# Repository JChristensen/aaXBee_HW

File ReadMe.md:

# Double-A XBee Sensor Node #
http://github.com/JChristensen/aaXBee_HW  
ReadMe file  
Jack Christensen Mar 2015  

## Introduction ##
A low-power, [Arduino](http://www.arduino.cc/)-compatible [XBee](http://www.digi.com/products/wireless-wired-embedded-solutions/zigbee-rf-modules/zigbee-mesh-module/xbee-zb-module) sensor node that runs on two AA cells. It should run for over a year on a pair of AA alkaline cells (this could be reduced if sensors that require relatively large amounts of power or on-time are used). For an example sketch, see the [aaXBee sketch](https://github.com/JChristensen/GroveStreams/tree/master/examples/aaXBee) in my [GroveStreams library](https://github.com/JChristensen/GroveStreams). The AA XBee Node will send data to an Arduino running the [gsGateway sketch](https://github.com/JChristensen/GroveStreams/tree/master/examples/gsGateway), which forwards it to the [GroveStreams](https://grovestreams.com/) web site. (Also see my blog post, [A GroveStreams Wireless Sensor Network](http://adventuresinarduinoland.blogspot.com/2015/05/a-grovestreams-wireless-sensor-network.html).)

The AA XBee Node includes an accurate real-time clock ([DS3231](http://www.maximintegrated.com/en/products/digital/real-time-clocks/DS3231.html), ±2ppm from 0°C to +40°C) for precise timing of data transmissions and an accurate on-board I2C temperature sensor ([MCP9808](http://www.microchip.com/MCP9808), ±0.25°C typical). A prototyping area is provided for connecting additional sensors. Twelve microcontroller GPIO pins are available to interface with sensors, including the I2C and SPI buses and analog inputs. A pushbutton switch and an LED are available for application use.

## Features ##
The Double-A XBee Sensor Node is a flexible design with three major configuration options based on the voltage and power required by application-specific sensors. One or two boost regulators are used to supply 3.3V to the XBee and either 3.3V or 5V to the MCU and sensors.These configurations are summarized on page 2 of the [aaXBee_BOM.pdf](http://github.com/JChristensen/aaXBee_HW/raw/master/aaXBee_BOM.pdf) file.

Various components are also optional depending on requirements. See page 3 of the [aaXBee_BOM.pdf](http://github.com/JChristensen/aaXBee_HW/raw/master/aaXBee_BOM.pdf) file for comments on optional components.

To conserve power, the AA XBee Node disables the boost regulator(s) and sleeps using the battery voltage directly (sleep current is < 5µA). With the regulator(s) disabled, the MCU's clock speed is reduced to avoid overclocking. Because of this, the board should be programmed with an in-circuit serial programmer (ICSP, e.g. AVRISP mkII, USBtinyISP, USBasp, etc.) as opposed to a bootloader. As part of this approach, specific fuse settings are required, so a custom entry in the Arduino boards.txt file is also recommended as follows:
```
##############################################################
aaDL.name=Double-A Datalogger/Double-A XBee Node
aaDL.upload.protocol=arduino
aaDL.upload.maximum_size=32768
aaDL.bootloader.low_fuses=0x7f
aaDL.bootloader.high_fuses=0xde
aaDL.bootloader.extended_fuses=0x06
aaDL.build.mcu=atmega328p
aaDL.build.f_cpu=8000000L
aaDL.build.core=arduino
aaDL.build.variant=standard
##############################################################
```

## CC BY-SA ##
"Double-A XBee Sensor Node" by Jack Christensen is licensed under [CC BY-SA 4.0](http://creativecommons.org/licenses/by-sa/4.0/).

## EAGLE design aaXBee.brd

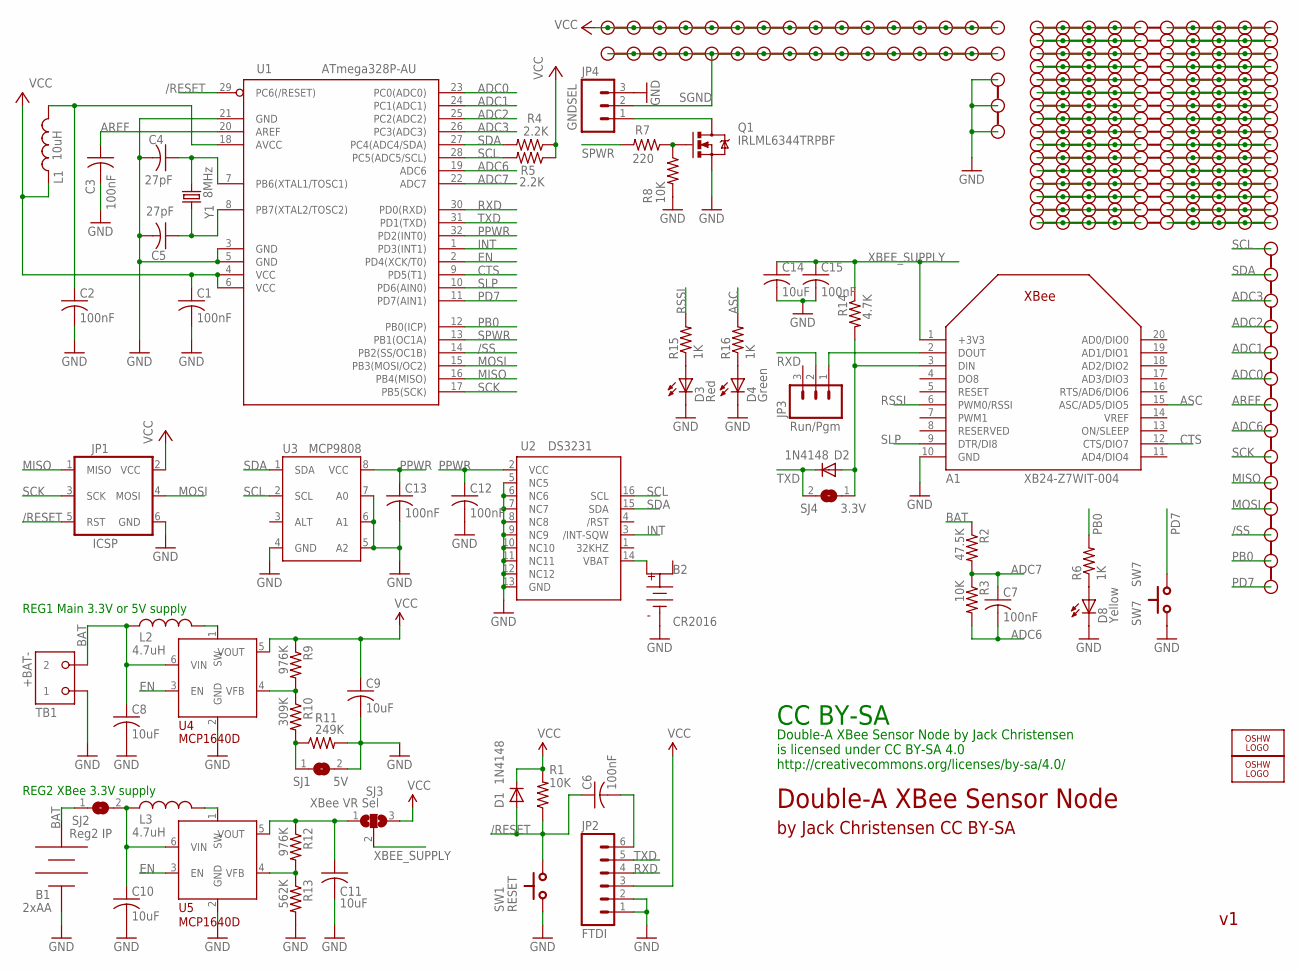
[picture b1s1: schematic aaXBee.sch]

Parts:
A1: XB24-Z7WIT-004; XBEE_OVAL_PADS
B1: 2xAA; KEYSTONE-2462-NO-HOLES
B2: CR2016; BAT-HLD-002-SMT
C1, C2, C3, C6, C7, C12, C13, C15: 100nF; M0805
C4, C5: 27pF; M0805
C8, C9, C10, C11, C14: 10uF; M0805
D1, D2: 1N4148; SOD-323F-A
D3: Red; D0805A
D4: Green; D0805
D8: Yellow; D0805A
JP1: ICSP; 2X3_LOCK
JP2: FTDI; 1X06_LOCK
JP3: Run/Pgm; 1X03_LOCK
JP4: GNDSEL; 1X03_LOCK
L1: 10uH; M0805
L2, L3: 4.7uH; NRS4018
LOGO1, LOGO2: OSHW_LOGO_8MILX0150-NT; OSHW_8X150_NOTEXT
PR1, PR2, PR3, PR4, PR5, PR6, PR7, PR8, PR9, PR10, PR11, PR12, PR14, PR15, PR16, PR17: PROTO-10
PR13: GND; PROTO-3
PR18: Proto ground; PROTO-16
PR19: Proto Vcc; PROTO-16
PR20: Signals; PROTO-14-NR
Q1: IRLML6344TRPBF; SOT23
R1, R3, R8: 10K; M0805
R2: 47.5K; M0805
R4, R5: 2.2K; M0805
R6, R15, R16: 1K; M0805
R7: 220; M0805
R9, R12: 976K; M0805
R10: 309K; M0805
R11: 249K; M0805
R13: 562K; M0805
R14: 4.7K; M0805
SJ1: 5V; SJ
SJ2: Reg2 IP; SJ
SJ3: XBee VR Sel; SJ_2
SJ4: 3.3V; SJ
SW1: RESET; SWITCH-TACT-6X3.5-SMT
SW7: SW7; SWITCH-TACT-6X3.5-SMT
TB1: +BAT-; OST-TB-2-3.5MM
U1: ATmega328P-AU; TQFP32-08
U2: DS3231; SO-16DW
U3: MCP9808; MSOP8
U4, U5: MCP1640D; SOT23-6
Y1: 8MHz; CRYSTAL-ABRACON-ABM2

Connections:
/RESET: C6.1, D1.A, JP1.5 (RST), R1.1, SW1.P$1, U1.29 (PC6(/RESET))
/SS: PR20.3, U1.14 (PB2(SS/OC1B))
ADC0: PR20.9, U1.23 (PC0(ADC0))
ADC1: PR20.10, U1.24 (PC1(ADC1))
ADC2: PR20.11, U1.25 (PC2(ADC2))
ADC3: PR20.12, U1.26 (PC3(ADC3))
ADC6: C7.2, PR20.7, R3.2, U1.19 (ADC6)
ADC7: C7.1, R2.2, R3.1, U1.22 (ADC7)
AREF: C3.1, PR20.8, U1.20 (AREF)
ASC: A1.15 (ASC/AD5/DIO5), R16.2
BAT: B1.POS, C8.1, L2.P$1 (1), R2.1, SJ2.1, TB1.P$2 (2), U4.6 (VIN)
CTS: A1.12 (CTS/DIO7), U1.9 (PD5(T1))
EN: U1.2 (PD4(XCK/T0)), U4.3 (EN), U5.3 (EN)
GND: A1.10 (GND), B1.NEG, B2.NEG (B-), C1.2, C2.2, C3.2, C4.2, C5.2, C8.2, C9.2, C10.2, C11.2, C12.2, C13.2, C14.2, C15.2, D3.K (C), D4.K (C), D8.K (C), JP1.6 (GND), JP2.1, JP2.2, JP4.3, PR13.1, PR13.2, PR13.3, Q1.2 (S), R8.2, R11.2, R13.2, SJ1.2, SW1.P$2, SW7.P$2, TB1.P$1 (1), U1.3 (GND), U1.5 (GND), U1.21 (GND), U2.5 (NC5), U2.6 (NC6), U2.7 (NC7), U2.8 (NC8), U2.9 (NC9), U2.10 (NC10), U2.11 (NC11), U2.12 (NC12), U2.13 (GND), U3.4 (GND), U3.5 (A2), U3.6 (A1), U3.7 (A0), U4.2 (GND), U5.2 (GND)
INT: U1.1 (PD3(INT1)), U2.3 (/INT-SQW)
MISO: JP1.1 (MISO), PR20.5, U1.16 (PB4(MISO))
MOSI: JP1.4 (MOSI), PR20.4, U1.15 (PB3(MOSI/OC2))
unnamed: B2.POS1, U2.14 (VBAT)
unnamed: D8.A, R6.1
unnamed: PR1.6, PR1.7, PR1.8, PR1.9, PR1.10
unnamed: PR5.6, PR5.7, PR5.8, PR5.9, PR5.10
unnamed: R9.2, R10.1, U4.4 (VFB)
unnamed: L2.P$2 (2), U4.1 (SW)
unnamed: R10.2, R11.1, SJ1.1
unnamed: PR2.6, PR2.7, PR2.8, PR2.9, PR2.10
unnamed: PR3.6, PR3.7, PR3.8, PR3.9, PR3.10
unnamed: R12.2, R13.1, U5.4 (VFB)
unnamed: L3.P$2 (2), U5.1 (SW)
unnamed: PR4.6, PR4.7, PR4.8, PR4.9, PR4.10
unnamed: PR6.6, PR6.7, PR6.8, PR6.9, PR6.10
unnamed: PR7.1, PR7.2, PR7.3, PR7.4, PR7.5
unnamed: PR8.1, PR8.2, PR8.3, PR8.4, PR8.5
unnamed: PR9.1, PR9.2, PR9.3, PR9.4, PR9.5
unnamed: PR10.1, PR10.2, PR10.3, PR10.4, PR10.5
unnamed: PR11.1, PR11.2, PR11.3, PR11.4, PR11.5
unnamed: PR12.1, PR12.2, PR12.3, PR12.4, PR12.5
unnamed: PR1.1, PR1.2, PR1.3, PR1.4, PR1.5
unnamed: PR2.1, PR2.2, PR2.3, PR2.4, PR2.5
unnamed: Q1.1 (G), R7.1, R8.1
unnamed: PR3.1, PR3.2, PR3.3, PR3.4, PR3.5
unnamed: PR4.1, PR4.2, PR4.3, PR4.4, PR4.5
unnamed: PR6.1, PR6.2, PR6.3, PR6.4, PR6.5
unnamed: PR7.6, PR7.7, PR7.8, PR7.9, PR7.10
unnamed: PR5.1, PR5.2, PR5.3, PR5.4, PR5.5
unnamed: PR8.6, PR8.7, PR8.8, PR8.9, PR8.10
unnamed: PR9.6, PR9.7, PR9.8, PR9.9, PR9.10
unnamed: PR10.6, PR10.7, PR10.8, PR10.9, PR10.10
unnamed: PR11.6, PR11.7, PR11.8, PR11.9, PR11.10
unnamed: PR12.6, PR12.7, PR12.8, PR12.9, PR12.10
unnamed: C10.1, L3.P$1 (1), SJ2.2, U5.6 (VIN)
unnamed: JP4.1, Q1.3 (D)
unnamed: A1.3 (DIN), D2.A, R14.2, SJ4.1
unnamed: A1.2 (DOUT), JP3.1
unnamed: C11.1, R12.1, SJ3.1, U5.5 (VOUT)
unnamed: PR14.1, PR14.2, PR14.3, PR14.4, PR14.5
unnamed: D3.A, R15.1
unnamed: D4.A, R16.1
unnamed: C4.1, U1.7 (PB6(XTAL1/TOSC1)), Y1.P$2 (2)
unnamed: C5.1, U1.8 (PB7(XTAL2/TOSC2)), Y1.P$1 (1)
unnamed: PR14.6, PR14.7, PR14.8, PR14.9, PR14.10
unnamed: C2.1, L1.2, U1.18 (AVCC)
unnamed: PR15.1, PR15.2, PR15.3, PR15.4, PR15.5
unnamed: PR15.6, PR15.7, PR15.8, PR15.9, PR15.10
unnamed: PR16.1, PR16.2, PR16.3, PR16.4, PR16.5
unnamed: PR16.6, PR16.7, PR16.8, PR16.9, PR16.10
unnamed: PR17.1, PR17.2, PR17.3, PR17.4, PR17.5
unnamed: PR17.6, PR17.7, PR17.8, PR17.9, PR17.10
PB0: PR20.2, R6.2, U1.12 (PB0(ICP))
PD7: PR20.1, SW7.P$1, U1.11 (PD7(AIN1))
PPWR: C12.1, C13.1, U1.32 (PD2(INT0)), U2.2 (VCC), U3.8 (VCC)
RSSI: A1.6 (PWM0/RSSI), R15.2
RST: C6.2, JP2.6
RXD: JP2.4, JP3.2, U1.30 (PD0(RXD))
SCK: JP1.3 (SCK), PR20.6, U1.17 (PB5(SCK))
SCL: PR20.14, R5.2, U1.28 (PC5(ADC5/SCL)), U2.16 (SCL), U3.2 (SCL)
SDA: PR20.13, R4.2, U1.27 (PC4(ADC4/SDA)), U2.15 (SDA), U3.1 (SDA)
SGND: JP4.2, PR18.1, PR18.2, PR18.3, PR18.4, PR18.5, PR18.6, PR18.7, PR18.8, PR18.9, PR18.10, PR18.11, PR18.12, PR18.13, PR18.14, PR18.15, PR18.16
SLP: A1.9 (DTR/DI8), U1.10 (PD6(AIN0))
SPWR: R7.2, U1.13 (PB1(OC1A))
TXD: D2.K, JP2.5, SJ4.2, U1.31 (PD1(TXD))
VCC: C1.1, C9.1, D1.K, JP1.2 (VCC), JP2.3, L1.1, PR19.1, PR19.2, PR19.3, PR19.4, PR19.5, PR19.6, PR19.7, PR19.8, PR19.9, PR19.10, PR19.11, PR19.12, PR19.13, PR19.14, PR19.15, PR19.16, R1.2, R4.1, R5.1, R9.1, SJ3.3, U1.4 (VCC), U1.6 (VCC), U4.5 (VOUT)
XBEE_SUPPLY: A1.1 (+3V3), C14.1, C15.1, R14.1, SJ3.2

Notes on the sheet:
Double-A XBee Sensor Node
by Jack Christensen CC BY-SA
Double-A XBee Sensor Node by Jack Christensen is licensed under CC BY-SA 4.0 http://creativecommons.org/licenses/by-sa/4.0/
CC BY-SA
REG1 Main 3.3V or 5V supply
REG2 XBee 3.3V supply

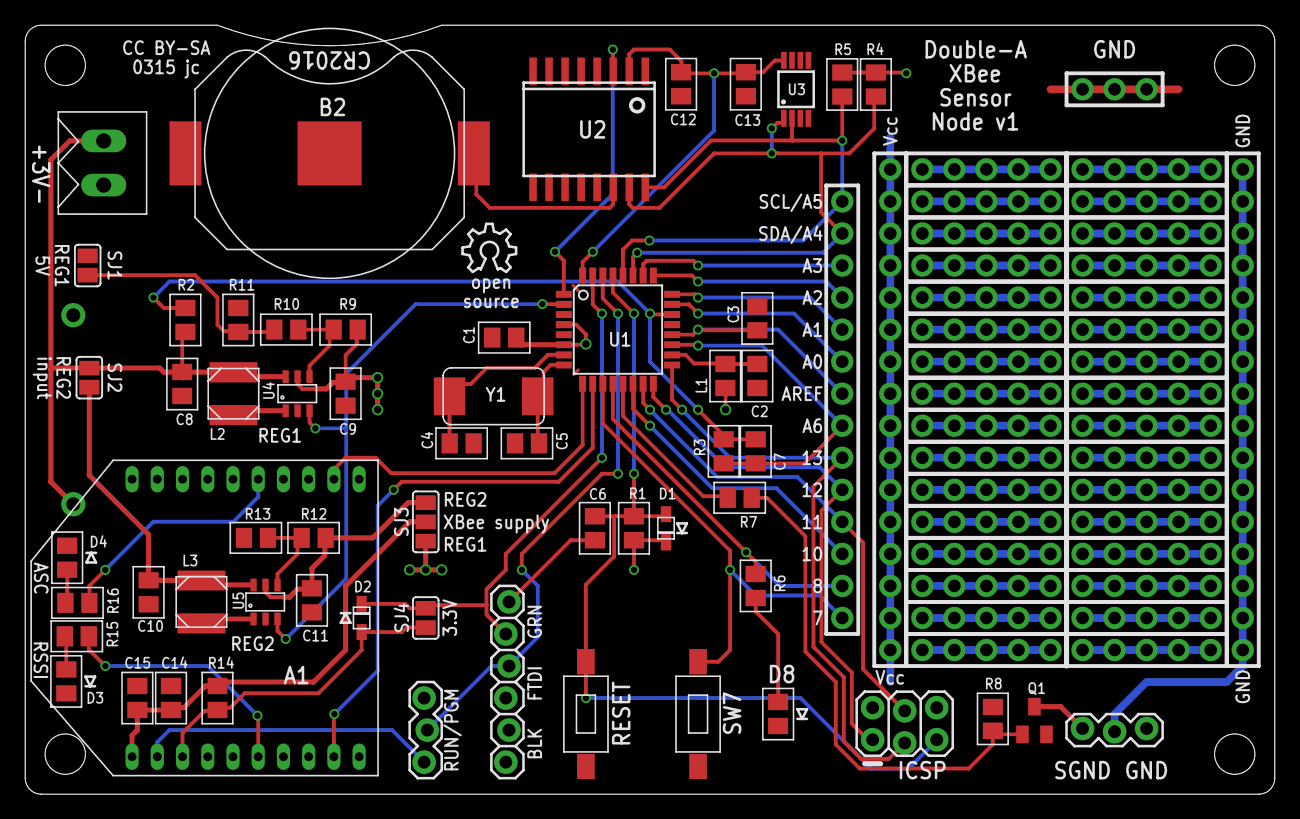
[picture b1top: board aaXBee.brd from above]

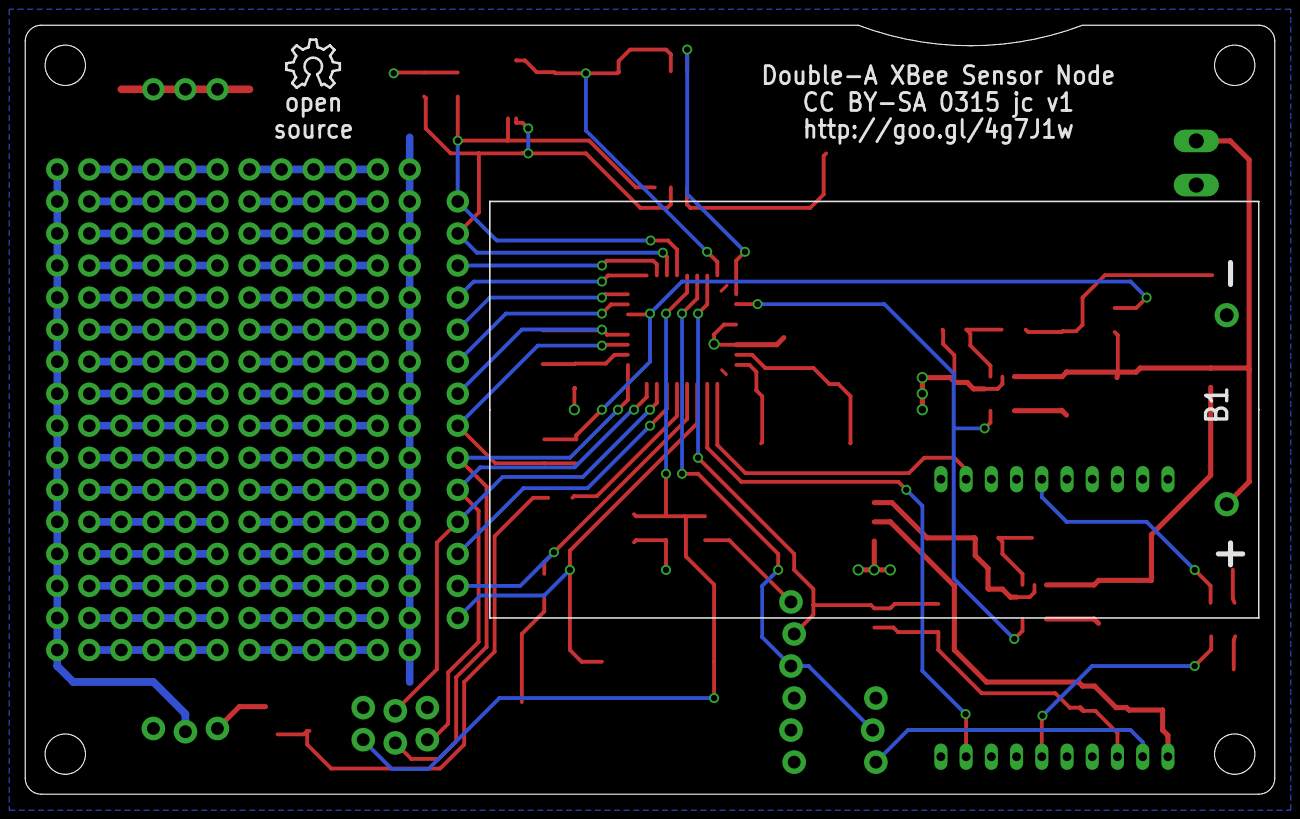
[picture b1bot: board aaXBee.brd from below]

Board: 2 copper layers, 99.1 x 61.0 mm, 82 parts (2 on the bottom side), 82 nets.

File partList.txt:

Partlist

Exported from aaXBee.sch at 6/6/2015 8:04:41 PM

EAGLE Version 6.4.0 Copyright (c) 1988-2013 CadSoft

Assembly variant: 

Part     Value          Device                   Package                Library  Sheet

A1       XB24-Z7WIT-004 ULINK_XBEEOVALPADS       XBEE_OVAL_PADS         _jc      1
B1       2xAA           BATTERY-2AANOHOLES       KEYSTONE-2462-NO-HOLES _jc      1
B2       CR2016         COIN-CELL-2016-SMT       BAT-HLD-002-SMT        _jc      1
C1       100nF          C-USM0805                M0805                  _jc      1
C2       100nF          C-USM0805                M0805                  _jc      1
C3       100nF          C-USM0805                M0805                  _jc      1
C4       27pF           C-USM0805                M0805                  _jc      1
C5       27pF           C-USM0805                M0805                  _jc      1
C6       100nF          C-USM0805                M0805                  _jc      1
C7       100nF          C-USM0805                M0805                  _jc      1
C8       10uF           C-USM0805                M0805                  _jc      1
C9       10uF           C-USM0805                M0805                  _jc      1
C10      10uF           C-USM0805                M0805                  _jc      1
C11      10uF           C-USM0805                M0805                  _jc      1
C12      100nF          C-USM0805                M0805                  _jc      1
C13      100nF          C-USM0805                M0805                  _jc      1
C14      10uF           C-USM0805                M0805                  _jc      1
C15      100nF          C-USM0805                M0805                  _jc      1
D1       1N4148         DIODESOD-323F-A          SOD-323F-A             _jc      1
D2       1N4148         DIODESOD-323F-A          SOD-323F-A             _jc      1
D3       Red            LEDD0805A                D0805A                 _jc      1
D4       Green          LEDD0805                 D0805                  _jc      1
D8       Yellow         LEDD0805A                D0805A                 _jc      1
JP1      ICSP           AVR_SPI_PRG_62X3_LOCK    2X3_LOCK               _jc      1
JP2      FTDI           M06LOCK                  1X06_LOCK              SparkFun 1
JP3      Run/Pgm        M03LOCK                  1X03_LOCK              SparkFun 1
JP4      GNDSEL         M03LOCK                  1X03_LOCK              SparkFun 1
L1       10uH           INDUCTORM0805            M0805                  _jc      1
L2       4.7uH          INDUCTORNRS4018          NRS4018                _jc      1
L3       4.7uH          INDUCTORNRS4018          NRS4018                _jc      1
PR1      PROTO-10       PROTO-10                 PROTO-10               _jc      1
PR2      PROTO-10       PROTO-10                 PROTO-10               _jc      1
PR3      PROTO-10       PROTO-10                 PROTO-10               _jc      1
PR4      PROTO-10       PROTO-10                 PROTO-10               _jc      1
PR5      PROTO-10       PROTO-10                 PROTO-10               _jc      1
PR6      PROTO-10       PROTO-10                 PROTO-10               _jc      1
PR7      PROTO-10       PROTO-10                 PROTO-10               _jc      1
PR8      PROTO-10       PROTO-10                 PROTO-10               _jc      1
PR9      PROTO-10       PROTO-10                 PROTO-10               _jc      1
PR10     PROTO-10       PROTO-10                 PROTO-10               _jc      1
PR11     PROTO-10       PROTO-10                 PROTO-10               _jc      1
PR12     PROTO-10       PROTO-10                 PROTO-10               _jc      1
PR13     GND            PROTO-3                  PROTO-3                _jc      1
PR14     PROTO-10       PROTO-10                 PROTO-10               _jc      1
PR15     PROTO-10       PROTO-10                 PROTO-10               _jc      1
PR16     PROTO-10       PROTO-10                 PROTO-10               _jc      1
PR17     PROTO-10       PROTO-10                 PROTO-10               _jc      1
PR18     Proto ground   PROTO-16                 PROTO-16               _jc      1
PR19     Proto Vcc      PROTO-16                 PROTO-16               _jc      1
PR20     Signals        PROTO-14NR               PROTO-14-NR            _jc      1
Q1       IRLML6344TRPBF MOSFET-NCHANNELSOT23     SOT23                  _jc      1
R1       10K            R-US_M0805               M0805                  _jc      1
R2       47.5K          R-US_M0805               M0805                  _jc      1
R3       10K            R-US_M0805               M0805                  _jc      1
R4       2.2K           R-US_M0805               M0805                  _jc      1
R5       2.2K           R-US_M0805               M0805                  _jc      1
R6       1K             R-US_M0805               M0805                  _jc      1
R7       220            R-US_M0805               M0805                  _jc      1
R8       10K            R-US_M0805               M0805                  _jc      1
R9       976K           R-US_M0805               M0805                  _jc      1
R10      309K           R-US_M0805               M0805                  _jc      1
R11      249K           R-US_M0805               M0805                  _jc      1
R12      976K           R-US_M0805               M0805                  _jc      1
R13      562K           R-US_M0805               M0805                  _jc      1
R14      4.7K           R-US_M0805               M0805                  _jc      1
R15      1K             R-US_M0805               M0805                  _jc      1
R16      1K             R-US_M0805               M0805                  _jc      1
SJ1      5V             SJ                       SJ                     jumper   1
SJ2      Reg2 IP        SJ                       SJ                     jumper   1
SJ3      XBee VR Sel    SJ2W                     SJ_2                   jumper   1
SJ4      3.3V           SJ                       SJ                     jumper   1
SW1      RESET          SPST-NO-MCTACT-6X3.5-SMT SWITCH-TACT-6X3.5-SMT  _jc      1
SW7      SW7            SPST-NO-MCTACT-6X3.5-SMT SWITCH-TACT-6X3.5-SMT  _jc      1
TB1      +BAT-          OST-TB-23.5MM            OST-TB-2-3.5MM         _jc      1
U1       ATmega328P-AU  MEGA8-AI                 TQFP32-08              atmel    1
U2       DS3231         DS3231                   SO-16DW                _jc      1
U3       MCP9808        MCP9808                  MSOP8                  _jc      1
U4       MCP1640D       MCP1640                  SOT23-6                _jc      1
U5       MCP1640D       MCP1640                  SOT23-6                _jc      1
Y1       8MHz           CRYSTALABM2              CRYSTAL-ABRACON-ABM2   _jc      1

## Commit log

2015-01-18 Initial commit.
2015-02-05 First reasonably complete routing.
2015-02-23 Routing complete.
2015-02-28 Tweak a few traces.
2015-02-28 Rename some components to be sequential. Cosmetic adjustments to schematic.
2015-03-20 As sent to fab.
2015-03-20 Update doc files, board and schematic images.
2015-03-21 New board image.
2015-03-21 Add Vcc & GND labels to proto area.
2015-03-21 Add configuration and optional component information to the Excel BoM workbook.
2015-06-06 Improved footprint for U3, change Q1 to Si2302CDS, added documentation and photos.
2015-06-07 Change Q1 to IRLML6344TRPBF.
2015-06-07 Update links in ReadMe.

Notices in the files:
aaXBee.brd:
CC BY-SA 0315 jc v1
